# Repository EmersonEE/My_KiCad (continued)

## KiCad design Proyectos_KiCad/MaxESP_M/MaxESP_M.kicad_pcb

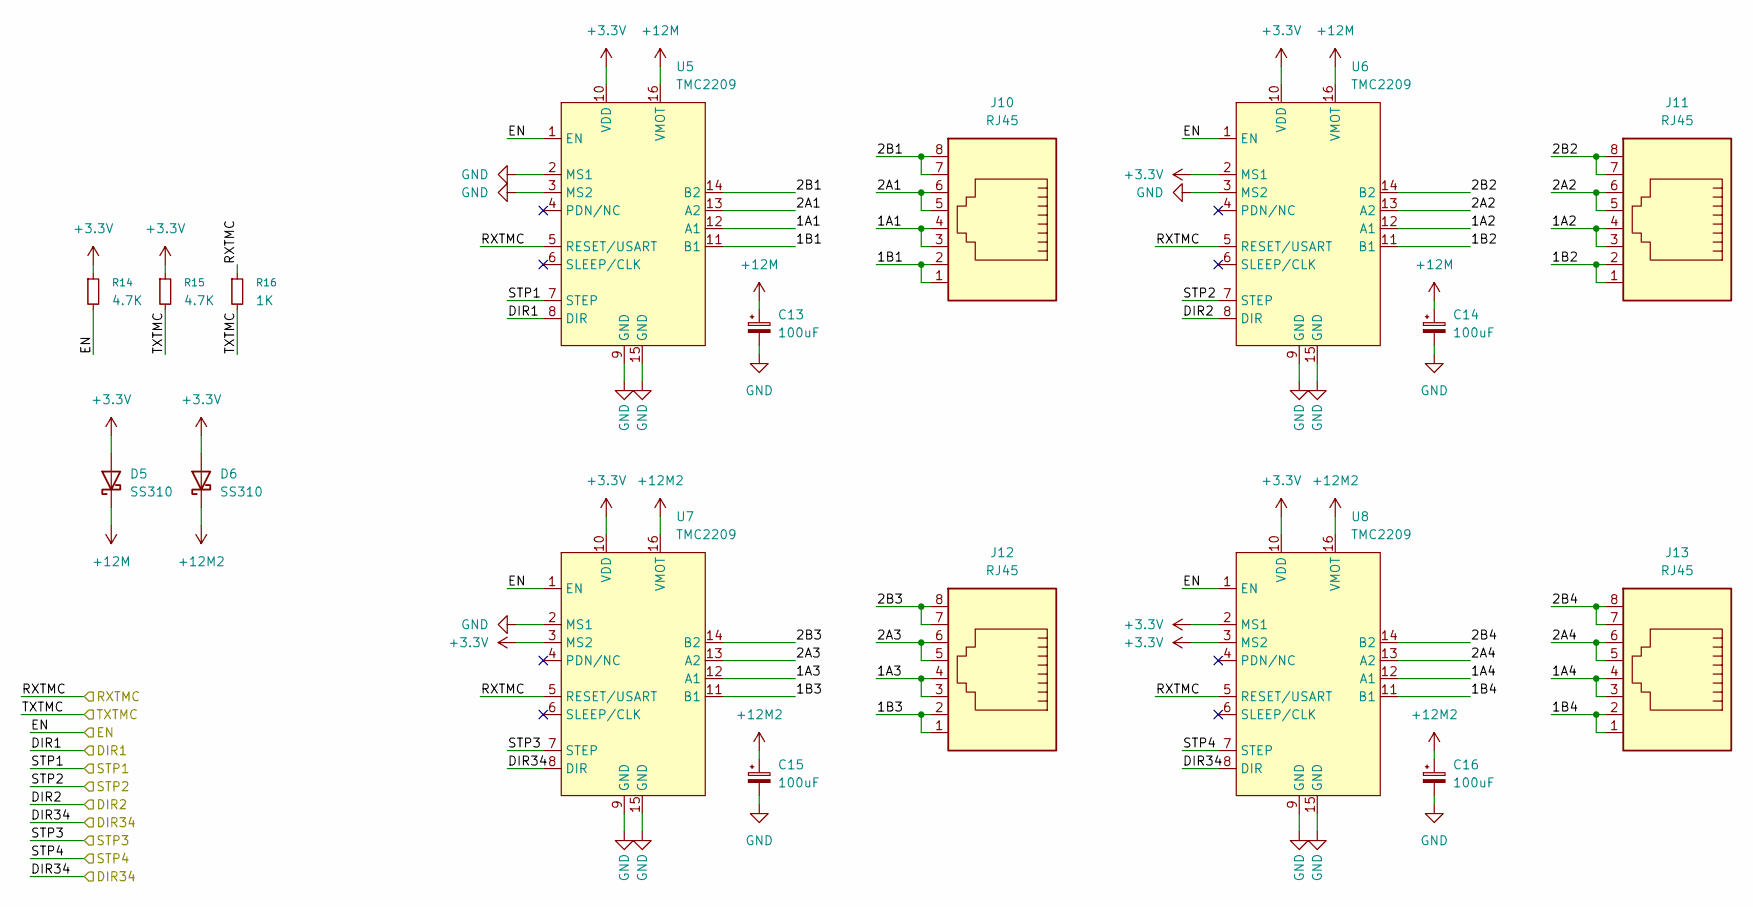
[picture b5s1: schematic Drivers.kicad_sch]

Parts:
C13, C14, C15, C16: 100uF; C_Elec_8x10.2
D5, D6: SS310; D_SMA
J10, J11, J12, J13: RJ45; RJ45_Amphenol_54602-x08_Horizontal
R14, R15: 4.7K; R_0805_2012Metric_Pad1.20x1.40mm_HandSolder
R16: 1K; R_0805_2012Metric_Pad1.20x1.40mm_HandSolder
U5, U6, U7, U8: TMC2209; D_TMC2209_Or

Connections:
+3.3V: D5.2 (A), D6.2 (A), R14.1, R15.1, U5.10 (VDD), U6.2 (MS1), U6.10 (VDD), U7.3 (MS2), U7.10 (VDD), U8.2 (MS1), U8.3 (MS2), U8.10 (VDD); also elsewhere on the board
+12M: C13.1, C14.1, D5.1 (K), U5.16 (VMOT), U6.16 (VMOT); also elsewhere on the board
+12M2: C15.1, C16.1, D6.1 (K), U7.16 (VMOT), U8.16 (VMOT); also elsewhere on the board
/Drivers/1A1: J10.3, J10.4, U5.12 (A1)
/Drivers/1A2: J11.3, J11.4, U6.12 (A1)
/Drivers/1A3: J12.3, J12.4, U7.12 (A1)
/Drivers/1A4: J13.3, J13.4, U8.12 (A1)
/Drivers/1B1: J10.1, J10.2, U5.11 (B1)
/Drivers/1B2: J11.1, J11.2, U6.11 (B1)
/Drivers/1B3: J12.1, J12.2, U7.11 (B1)
/Drivers/1B4: J13.1, J13.2, U8.11 (B1)
/Drivers/2A1: J10.5, J10.6, U5.13 (A2)
/Drivers/2A2: J11.5, J11.6, U6.13 (A2)
/Drivers/2A3: J12.5, J12.6, U7.13 (A2)
/Drivers/2A4: J13.5, J13.6, U8.13 (A2)
/Drivers/2B1: J10.7, J10.8, U5.14 (B2)
/Drivers/2B2: J11.7, J11.8, U6.14 (B2)
/Drivers/2B3: J12.7, J12.8, U7.14 (B2)
/Drivers/2B4: J13.7, J13.8, U8.14 (B2)
/Drivers/DIR1: U5.8 (DIR); also elsewhere on the board
/Drivers/DIR2: U6.8 (DIR); also elsewhere on the board
/Drivers/DIR34: U7.8 (DIR), U8.8 (DIR); also elsewhere on the board
/Drivers/EN: R14.2, U5.1 (EN), U6.1 (EN), U7.1 (EN), U8.1 (EN); also elsewhere on the board
/Drivers/RXTMC: R16.1, U5.5 (RESET/USART), U6.5 (RESET/USART), U7.5 (RESET/USART), U8.5 (RESET/USART); also elsewhere on the board
/Drivers/STP1: U5.7 (STEP); also elsewhere on the board
/Drivers/STP2: U6.7 (STEP); also elsewhere on the board
/Drivers/STP3: U7.7 (STEP); also elsewhere on the board
/Drivers/STP4: U8.7 (STEP); also elsewhere on the board
/Drivers/TXTMC: R15.2, R16.2; also elsewhere on the board
GND: C13.2, C14.2, C15.2, C16.2, U5.2 (MS1), U5.3 (MS2), U5.9 (GND), U5.15 (GND), U6.3 (MS2), U6.9 (GND), U6.15 (GND), U7.2 (MS1), U7.9 (GND), U7.15 (GND), U8.9 (GND), U8.15 (GND); also elsewhere on the board

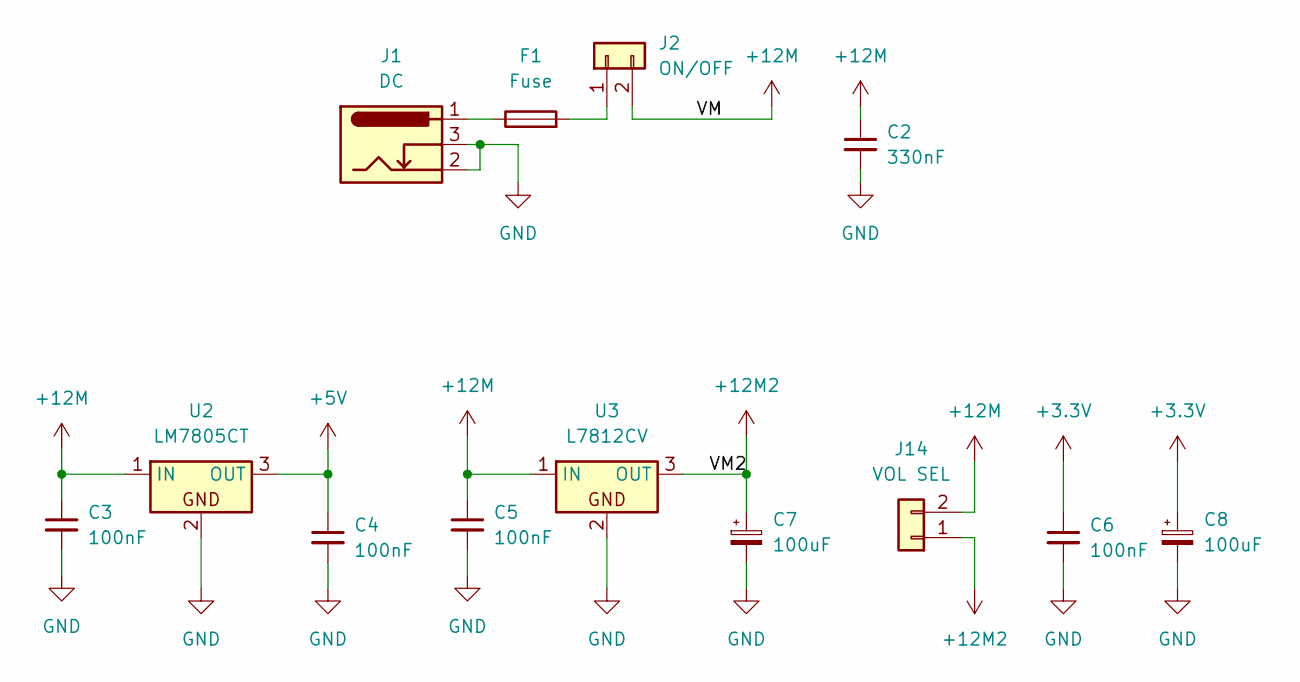
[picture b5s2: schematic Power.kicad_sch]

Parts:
C2: 330nF; C_0805_2012Metric_Pad1.18x1.45mm
C3, C4, C5, C6: 100nF; C_0805_2012Metric_Pad1.18x1.45mm
C7, C8: 100uF; C_0805_2012Metric_Pad1.18x1.45mm
F1: Fuse; Fuse_5x22mm
J1: DC; BarrelJack_Horizontal
J2: ON/OFF; Molex_KK-254_AE-6410-02A_1x02_P2.54mm_Vertical
J14: VOL SEL; PinHeader_1x02_P2.54mm_Vertical
U2: LM7805CT; TO-220-3_Vertical
U3: L7812CV; TO-220-3_Vertical

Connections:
+3.3V: C6.1, C8.1; also elsewhere on the board
+5V: C4.1, U2.3 (OUT); also elsewhere on the board
+12M: C2.1, C3.1, C5.1, J2.2, J14.2, U2.1 (IN), U3.1 (IN); also elsewhere on the board
+12M2: C7.1, J14.1, U3.3 (OUT); also elsewhere on the board
GND: C2.2, C3.2, C4.2, C5.2, C6.2, C7.2, C8.2, J1.2, J1.3, U2.2, U3.2; also elsewhere on the board
unnamed: F1.1, J1.1
unnamed: F1.2, J2.1

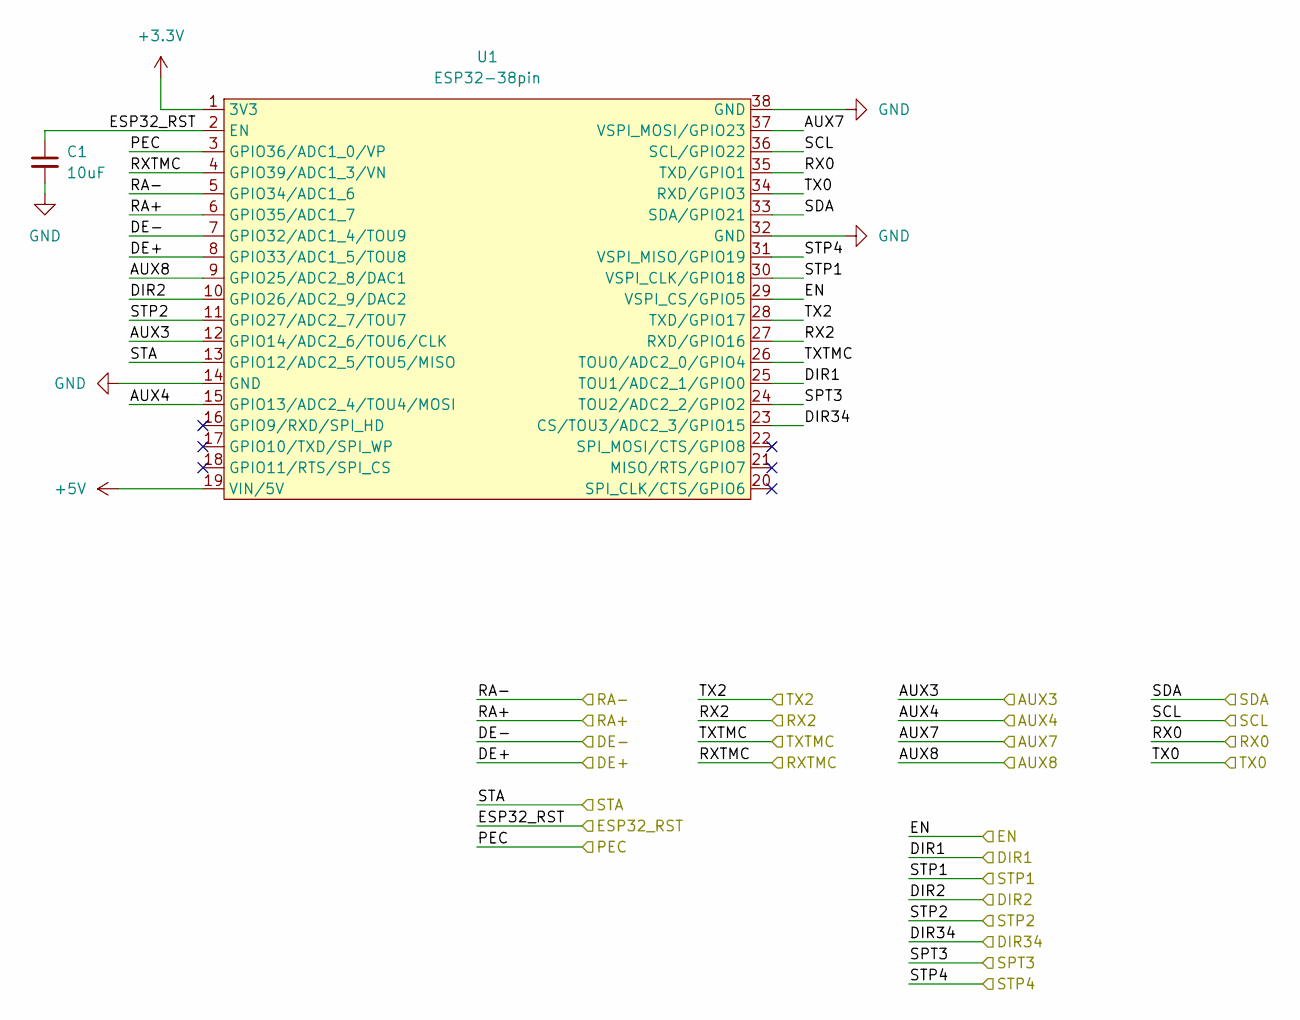
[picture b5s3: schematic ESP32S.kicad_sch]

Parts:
C1: 10uF; C_Elec_8x6.2
U1: ESP32-38pin; NODEMCU-ESP32S-NARROW

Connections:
+3.3V: U1.1 (3V3); also elsewhere on the board
+5V: U1.19 (VIN/5V); also elsewhere on the board
/Drivers/DIR1: U1.25 (TOU1/ADC2_1/GPIO0); also elsewhere on the board
/Drivers/DIR2: U1.10 (GPIO26/ADC2_9/DAC2); also elsewhere on the board
/Drivers/DIR34: U1.23 (CS/TOU3/ADC2_3/GPIO15); also elsewhere on the board
/Drivers/EN: U1.29 (VSPI_CS/GPIO5); also elsewhere on the board
/Drivers/RXTMC: U1.4 (GPIO39/ADC1_3/VN); also elsewhere on the board
/Drivers/STP1: U1.30 (VSPI_CLK/GPIO18); also elsewhere on the board
/Drivers/STP2: U1.11 (GPIO27/ADC2_7/TOU7); also elsewhere on the board
/Drivers/STP3: U1.24 (TOU2/ADC2_2/GPIO2); also elsewhere on the board
/Drivers/STP4: U1.31 (VSPI_MISO/GPIO19); also elsewhere on the board
/Drivers/TXTMC: U1.26 (TOU0/ADC2_0/GPIO4); also elsewhere on the board
/ESP32S/AUX3: U1.12 (GPIO14/ADC2_6/TOU6/CLK); also elsewhere on the board
/ESP32S/AUX4: U1.15 (GPIO13/ADC2_4/TOU4/MOSI); also elsewhere on the board
/ESP32S/AUX7: U1.37 (VSPI_MOSI/GPIO23); also elsewhere on the board
/ESP32S/AUX8: U1.9 (GPIO25/ADC2_8/DAC1); also elsewhere on the board
/ESP32S/DE+: U1.8 (GPIO33/ADC1_5/TOU8); also elsewhere on the board
/ESP32S/DE-: U1.7 (GPIO32/ADC1_4/TOU9); also elsewhere on the board
/ESP32S/ESP32_RST: C1.1, U1.2 (EN)
/ESP32S/PEC: U1.3 (GPIO36/ADC1_0/VP); also elsewhere on the board
/ESP32S/RA+: U1.6 (GPIO35/ADC1_7); also elsewhere on the board
/ESP32S/RA-: U1.5 (GPIO34/ADC1_6); also elsewhere on the board
/ESP32S/RX0: U1.35 (TXD/GPIO1)
/ESP32S/RX2: U1.27 (RXD/GPIO16); also elsewhere on the board
/ESP32S/SCL: U1.36 (SCL/GPIO22); also elsewhere on the board
/ESP32S/SDA: U1.33 (SDA/GPIO21); also elsewhere on the board
/ESP32S/STA: U1.13 (GPIO12/ADC2_5/TOU5/MISO); also elsewhere on the board
/ESP32S/TX0: U1.34 (RXD/GPIO3)
/ESP32S/TX2: U1.28 (TXD/GPIO17); also elsewhere on the board
GND: C1.2, U1.14 (GND), U1.32 (GND), U1.38 (GND); also elsewhere on the board

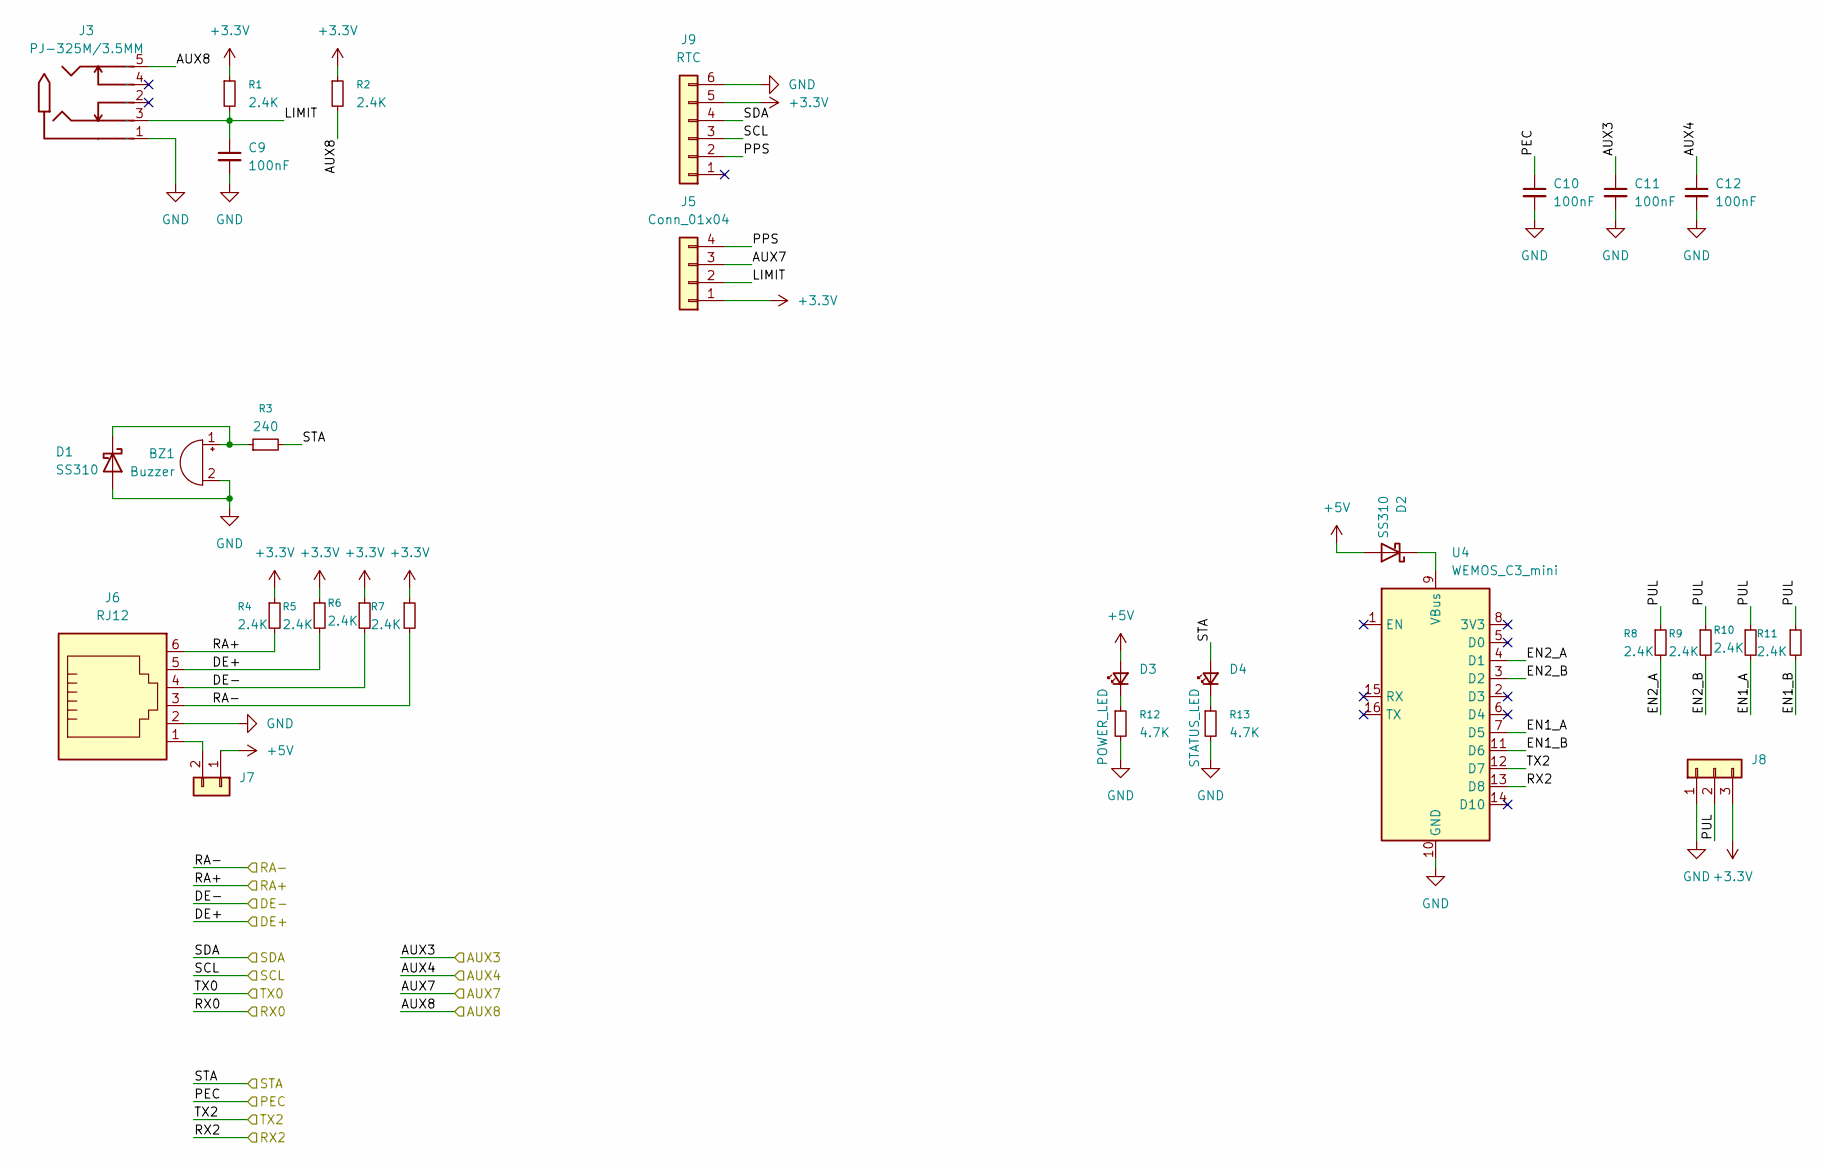
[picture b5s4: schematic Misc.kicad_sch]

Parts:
BZ1: Buzzer; Buzzer_12x9.5RM7.6
C9, C10, C11, C12: 100nF; C_0805_2012Metric_Pad1.18x1.45mm
D1, D2: SS310; D_SMA
D3: POWER_LED; LED_0805_2012Metric_Pad1.15x1.40mm
D4: STATUS_LED; LED_0805_2012Metric_Pad1.15x1.40mm
J3: PJ-325M/3.5MM; Jack_3.5mm_CUI_SJ1-3535NG_Horizontal; Manufacturer Part PJ-325M/3.5MM
J5: Conn_01x04; PinHeader_1x04_P2.54mm_Vertical
J6: RJ12; RJ12_Amphenol_54601-x06_Horizontal
J7: Molex_KK-254_AE-6410-02A_1x02_P2.54mm_Vertical
J8: PinHeader_1x03_P2.54mm_Vertical
J9: RTC; DS3231-RTC-24C32-EEPROM-SINGLE-HEADER
R1, R2, R4, R5, R6, R7, R8, R9, R10, R11: 2.4K; R_0805_2012Metric_Pad1.20x1.40mm_HandSolder
R3: 240; R_0805_2012Metric_Pad1.20x1.40mm_HandSolder
R12, R13: 4.7K; R_0805_2012Metric_Pad1.20x1.40mm_HandSolder
U4: WEMOS_C3_mini

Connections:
+3.3V: J5.1, J8.3, J9.5, R1.1, R2.1, R4.1, R5.1, R6.1, R7.1; also elsewhere on the board
+5V: D2.2 (A), D3.2 (A), J7.1; also elsewhere on the board
/ESP32S/AUX3: C11.1; also elsewhere on the board
/ESP32S/AUX4: C12.1; also elsewhere on the board
/ESP32S/AUX7: J5.3; also elsewhere on the board
/ESP32S/AUX8: J3.5, R2.2; also elsewhere on the board
/ESP32S/DE+: J6.5, R5.2; also elsewhere on the board
/ESP32S/DE-: J6.4, R6.2; also elsewhere on the board
/ESP32S/PEC: C10.1; also elsewhere on the board
/ESP32S/RA+: J6.6, R4.2; also elsewhere on the board
/ESP32S/RA-: J6.3, R7.2; also elsewhere on the board
/ESP32S/RX2: U4.13 (D8); also elsewhere on the board
/ESP32S/SCL: J9.3; also elsewhere on the board
/ESP32S/SDA: J9.4; also elsewhere on the board
/ESP32S/STA: D4.2 (A), R3.2; also elsewhere on the board
/ESP32S/TX2: U4.12 (D7); also elsewhere on the board
/Misc/EN1_A: R10.2, U4.7 (D5)
/Misc/EN1_B: R11.2, U4.11 (D6)
/Misc/EN2_A: R8.2, U4.4 (D1)
/Misc/EN2_B: R9.2, U4.3 (D2)
/Misc/LIMIT: C9.1, J3.3, J5.2, R1.2
/Misc/PPS: J5.4, J9.2
/Misc/PUL: J8.2, R8.1, R9.1, R10.1, R11.1
GND: BZ1.2 (-), C9.2, C10.2, C11.2, C12.2, D1.2 (A), J3.1, J6.2, J8.1, J9.6, R12.2, R13.2, U4.10 (GND); also elsewhere on the board
unnamed: BZ1.1 (+), D1.1 (K), R3.1
unnamed: D2.1 (K), U4.9 (VBus)
unnamed: D3.1 (K), R12.1
unnamed: D4.1 (K), R13.1
unnamed: J6.1, J7.2

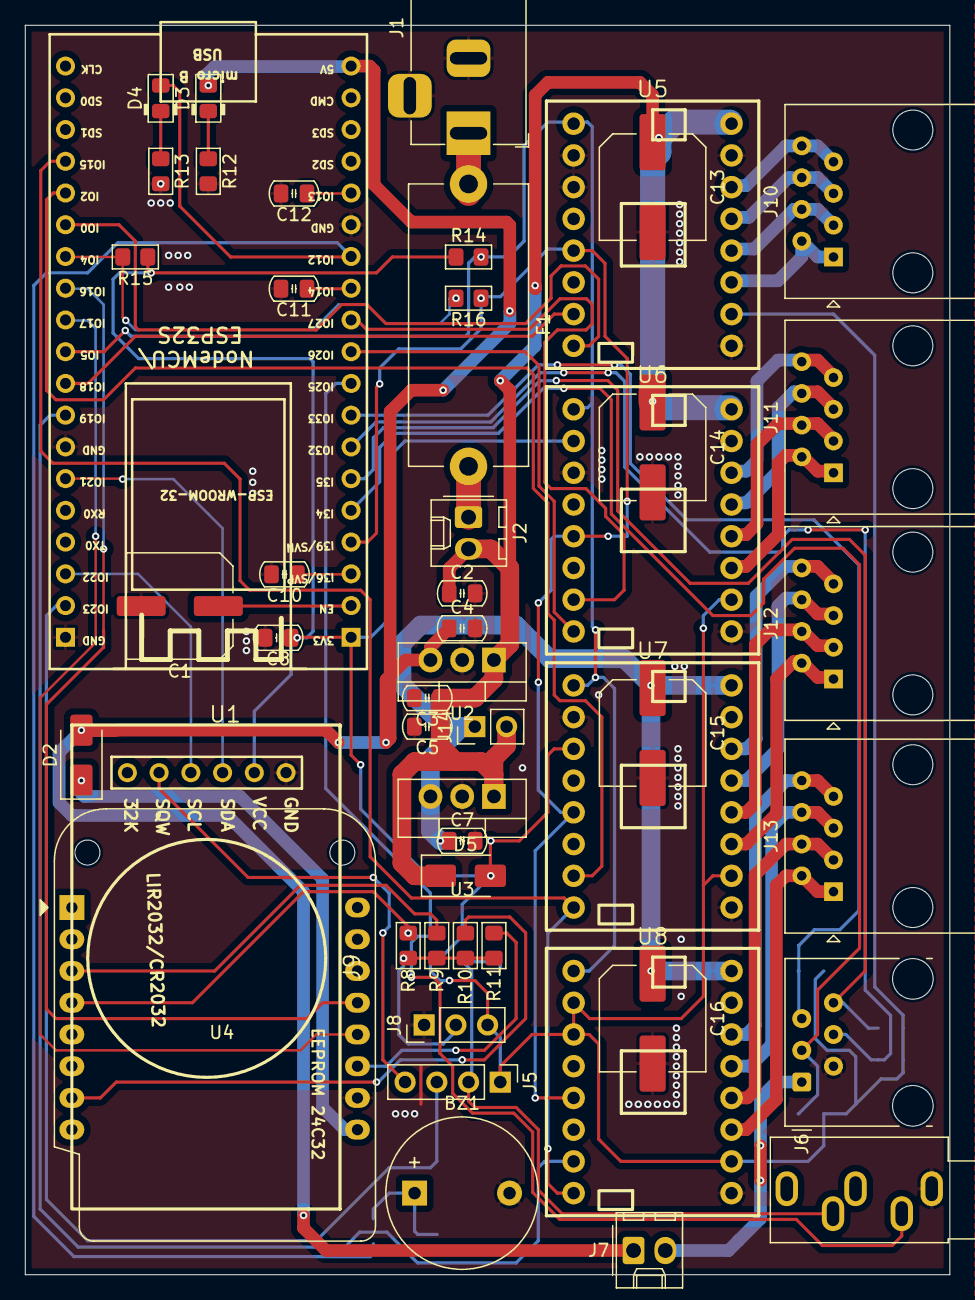
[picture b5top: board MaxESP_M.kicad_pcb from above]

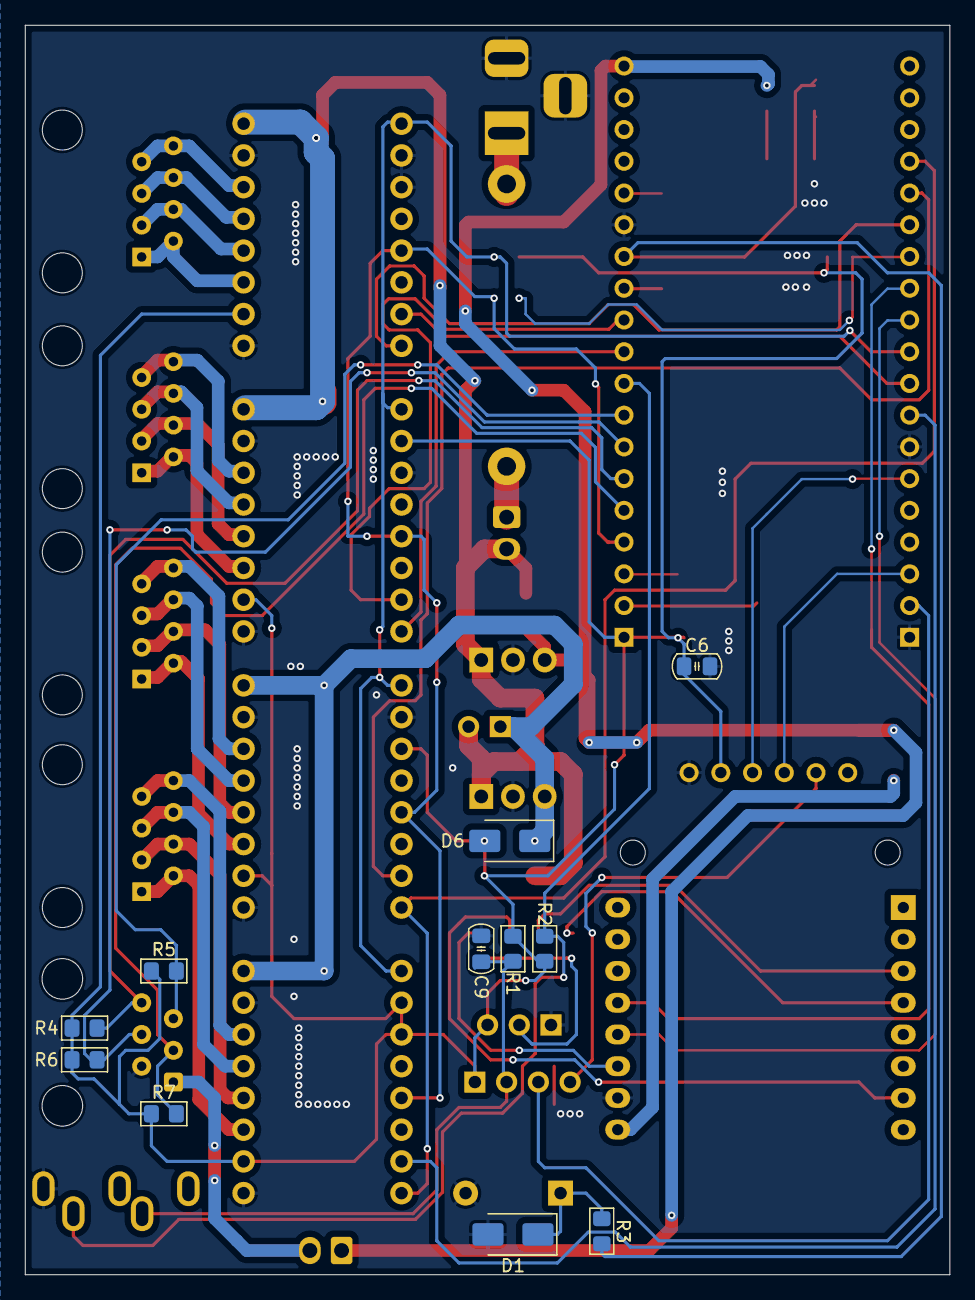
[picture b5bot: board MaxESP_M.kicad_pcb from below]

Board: 2 copper layers, 74.0 x 100.0 mm, 61 parts (11 on the bottom side), 60 nets.

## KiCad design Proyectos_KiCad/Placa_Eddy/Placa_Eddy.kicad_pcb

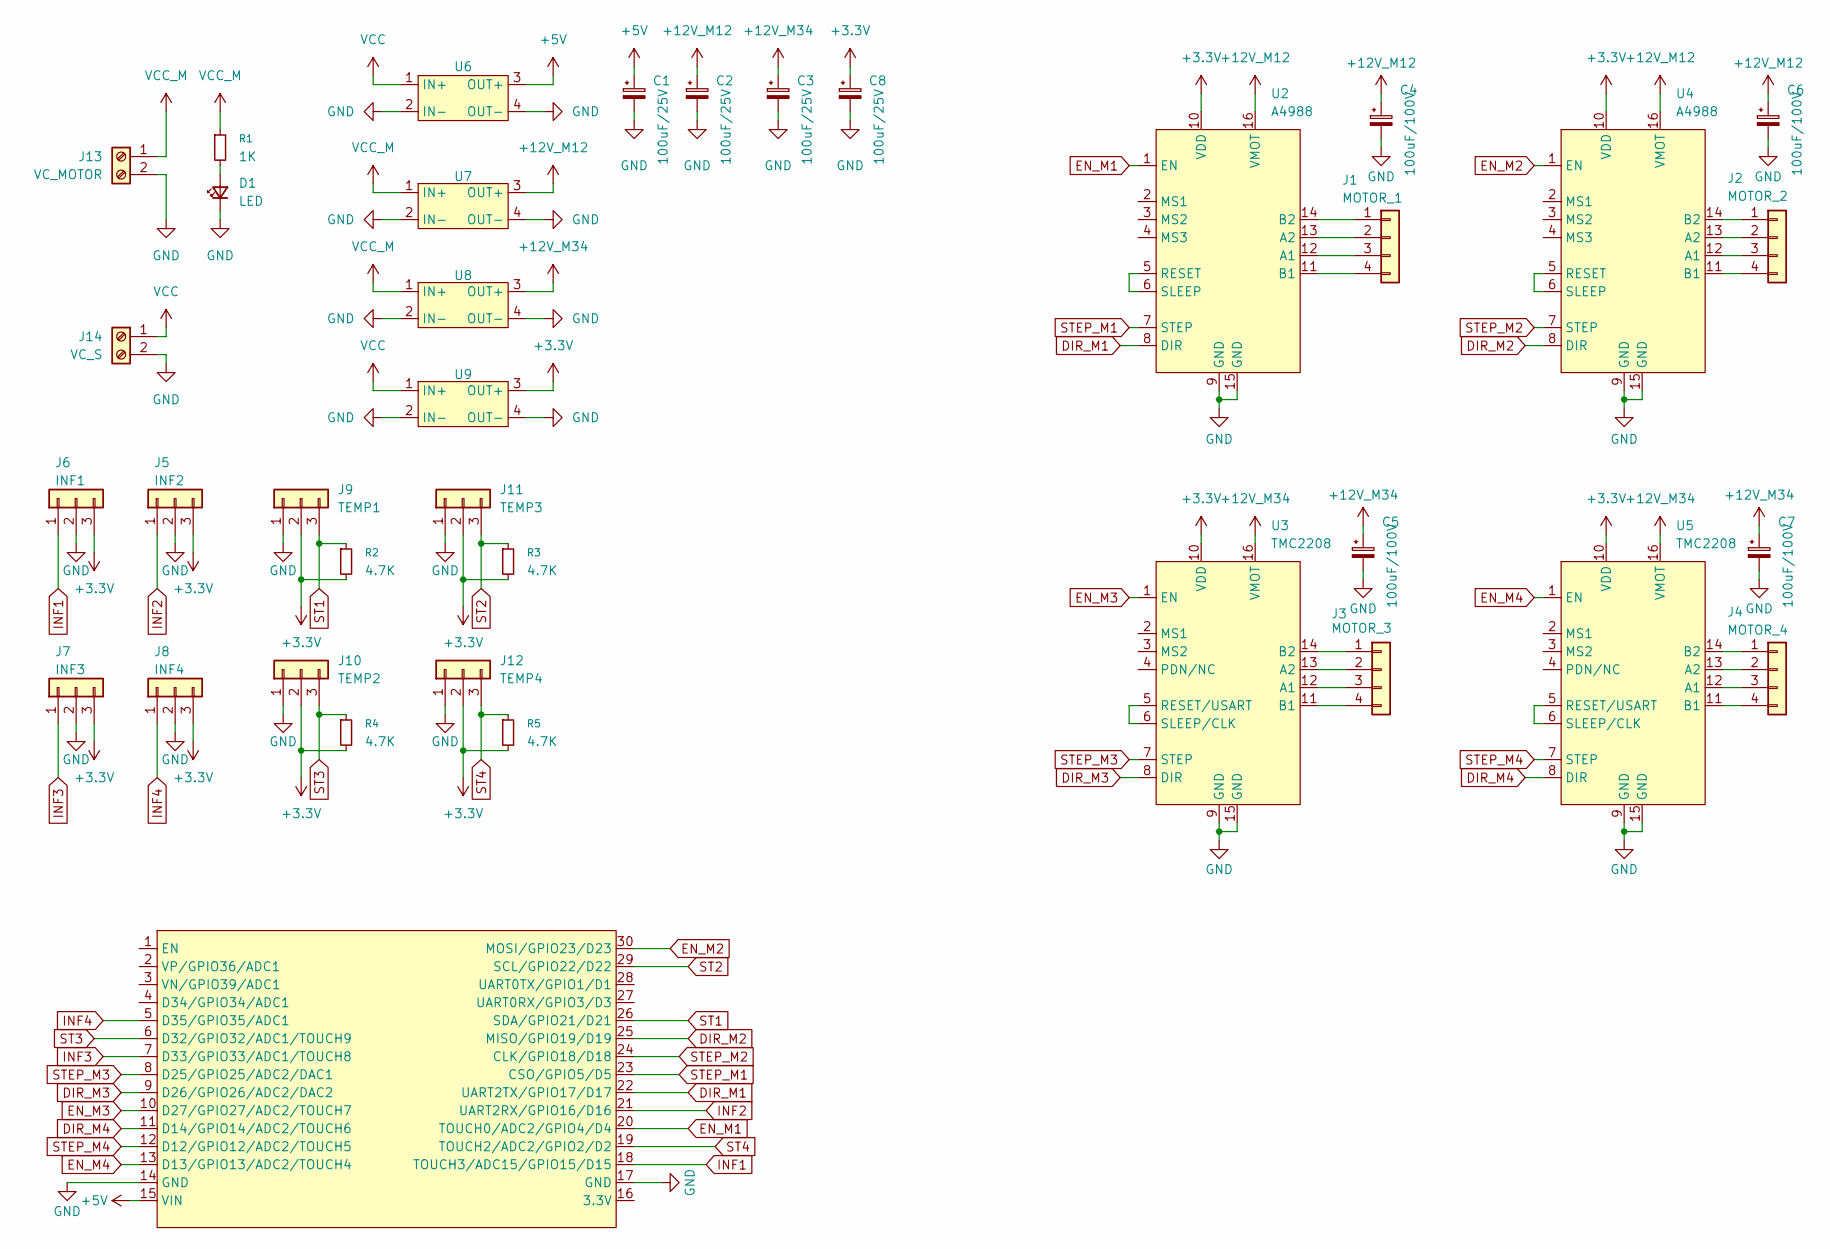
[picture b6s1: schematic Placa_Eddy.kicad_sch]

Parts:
C1, C2, C3, C8: 100uF/25V; CP_Elec_5x5.4
C4, C5, C6, C7: 100uF/100V; CP_Elec_5x5.4
D1: LED; LED_D5.0mm
J1: MOTOR_1; Molex_KK-254_AE-6410-04A_1x04_P2.54mm_Vertical; Part Number 1-0401FBV0T
J2: MOTOR_2; Molex_KK-254_AE-6410-04A_1x04_P2.54mm_Vertical; Part Number 1-0401FBV0T
J3: MOTOR_3; Molex_KK-254_AE-6410-04A_1x04_P2.54mm_Vertical; Part Number 1-0401FBV0T
J4: MOTOR_4; Molex_KK-254_AE-6410-04A_1x04_P2.54mm_Vertical; Part Number 1-0401FBV0T
J5: INF2; Molex_KK-254_AE-6410-03A_1x03_P2.54mm_Vertical; Part Number 1-0301FBV0T
J6: INF1; Molex_KK-254_AE-6410-03A_1x03_P2.54mm_Vertical; Part Number 1-0301FBV0T
J7: INF3; Molex_KK-254_AE-6410-03A_1x03_P2.54mm_Vertical; Part Number 1-0301FBV0T
J8: INF4; Molex_KK-254_AE-6410-03A_1x03_P2.54mm_Vertical; Part Number 1-0301FBV0T
J9: TEMP1; Molex_KK-254_AE-6410-03A_1x03_P2.54mm_Vertical; Part Number 1-0301FBV0T
J10: TEMP2; Molex_KK-254_AE-6410-03A_1x03_P2.54mm_Vertical; Part Number 1-0301FBV0T
J11: TEMP3; Molex_KK-254_AE-6410-03A_1x03_P2.54mm_Vertical; Part Number 1-0301FBV0T
J12: TEMP4; Molex_KK-254_AE-6410-03A_1x03_P2.54mm_Vertical; Part Number 1-0301FBV0T
J13: VC_MOTOR; TerminalBlock_Phoenix_MKDS-1,5-2_1x02_P5.00mm_Horizontal
J14: VC_S; TerminalBlock_Phoenix_MKDS-1,5-2_1x02_P5.00mm_Horizontal
R1: 1K; R_1206_3216Metric_Pad1.30x1.75mm
R2, R3, R4, R5: 4.7K; R_1206_3216Metric_Pad1.30x1.75mm
U1: ESP32_DevKit_V1_DOIT; ESP32_DEVKIT_V1_E32
U2, U4: A4988
U3, U5: TMC2208; D_TMC2209_Ca
U6, U7, U8, U9: LM2596S

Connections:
+3.3V: C8.1, J5.3, J6.3, J7.3, J8.3, J9.2, J10.2, J11.2, J12.2, R2.2, R3.2, R4.2, R5.2, U2.10 (VDD), U3.10 (VDD), U4.10 (VDD), U5.10 (VDD), U9.3 (OUT+)
+5V: C1.1, U1.15 (VIN), U6.3 (OUT+)
+12V_M12: C2.1, C4.1, C6.1, U2.16 (VMOT), U4.16 (VMOT), U7.3 (OUT+)
+12V_M34: C3.1, C5.1, C7.1, U3.16 (VMOT), U5.16 (VMOT), U8.3 (OUT+)
DIR_M1: U1.22 (UART2TX/GPIO17/D17), U2.8 (DIR)
DIR_M2: U1.25 (MISO/GPIO19/D19), U4.8 (DIR)
DIR_M3: U1.9 (D26/GPIO26/ADC2/DAC2), U3.8 (DIR)
DIR_M4: U1.11 (D14/GPIO14/ADC2/TOUCH6), U5.8 (DIR)
EN_M1: U1.20 (TOUCH0/ADC2/GPIO4/D4), U2.1 (EN)
EN_M2: U1.30 (MOSI/GPIO23/D23), U4.1 (EN)
EN_M3: U1.10 (D27/GPIO27/ADC2/TOUCH7), U3.1 (EN)
EN_M4: U1.13 (D13/GPIO13/ADC2/TOUCH4), U5.1 (EN)
GND: C1.2, C2.2, C3.2, C4.2, C5.2, C6.2, C7.2, C8.2, D1.1 (K), J5.2, J6.2, J7.2, J8.2, J9.1, J10.1, J11.1, J12.1, J13.2, J14.2, U1.14 (GND), U1.17 (GND), U2.9 (GND), U2.15 (GND), U3.9 (GND), U3.15 (GND), U4.9 (GND), U4.15 (GND), U5.9 (GND), U5.15 (GND), U6.2 (IN-), U6.4 (OUT-), U7.2 (IN-), U7.4 (OUT-), U8.2 (IN-), U8.4 (OUT-), U9.2 (IN-), U9.4 (OUT-)
INF1: J6.1, U1.18 (TOUCH3/ADC15/GPIO15/D15)
INF2: J5.1, U1.21 (UART2RX/GPIO16/D16)
INF3: J7.1, U1.7 (D33/GPIO33/ADC1/TOUCH8)
INF4: J8.1, U1.5 (D35/GPIO35/ADC1)
unnamed: D1.2 (A), R1.2
unnamed: J1.1, U2.14 (B2)
unnamed: J1.2, U2.13 (A2)
unnamed: J1.3, U2.12 (A1)
unnamed: J1.4, U2.11 (B1)
unnamed: J2.1, U4.14 (B2)
unnamed: J2.2, U4.13 (A2)
unnamed: J2.3, U4.12 (A1)
unnamed: J2.4, U4.11 (B1)
unnamed: J3.1, U3.14 (B2)
unnamed: J3.2, U3.13 (A2)
unnamed: J3.3, U3.12 (A1)
unnamed: J3.4, U3.11 (B1)
unnamed: J4.1, U5.14 (B2)
unnamed: J4.2, U5.13 (A2)
unnamed: J4.3, U5.12 (A1)
unnamed: J4.4, U5.11 (B1)
unnamed: U2.5 (RESET), U2.6 (SLEEP)
unnamed: U3.5 (RESET/USART), U3.6 (SLEEP/CLK)
unnamed: U4.5 (RESET), U4.6 (SLEEP)
unnamed: U5.5 (RESET/USART), U5.6 (SLEEP/CLK)
ST1: J9.3, R2.1, U1.26 (SDA/GPIO21/D21)
ST2: J11.3, R3.1, U1.29 (SCL/GPIO22/D22)
ST3: J10.3, R4.1, U1.6 (D32/GPIO32/ADC1/TOUCH9)
ST4: J12.3, R5.1, U1.19 (TOUCH2/ADC2/GPIO2/D2)
STEP_M1: U1.23 (CSO/GPIO5/D5), U2.7 (STEP)
STEP_M2: U1.24 (CLK/GPIO18/D18), U4.7 (STEP)
STEP_M3: U1.8 (D25/GPIO25/ADC2/DAC1), U3.7 (STEP)
STEP_M4: U1.12 (D12/GPIO12/ADC2/TOUCH5), U5.7 (STEP)
VCC: J14.1, U6.1 (IN+), U9.1 (IN+)
VCC_M: J13.1, R1.1, U7.1 (IN+), U8.1 (IN+)

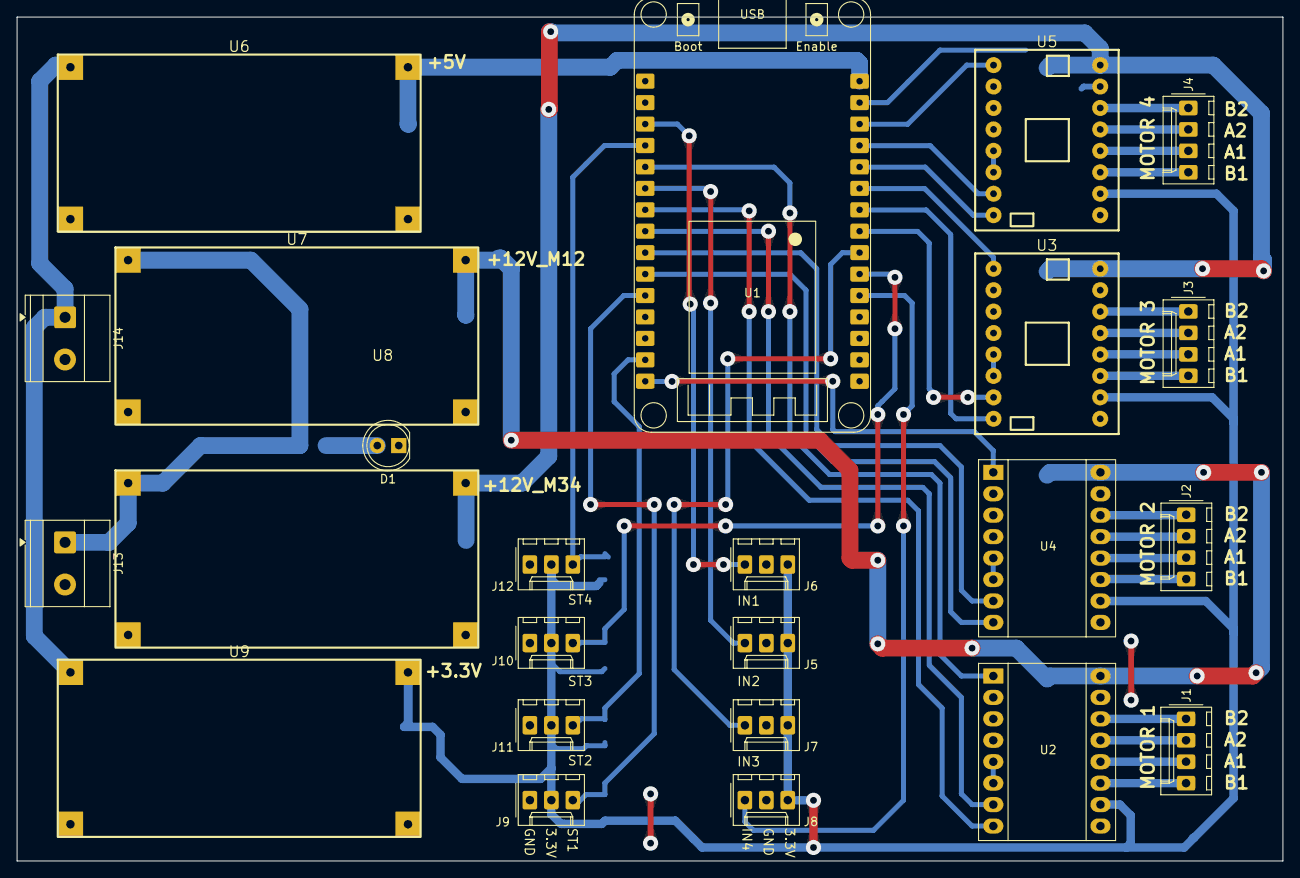
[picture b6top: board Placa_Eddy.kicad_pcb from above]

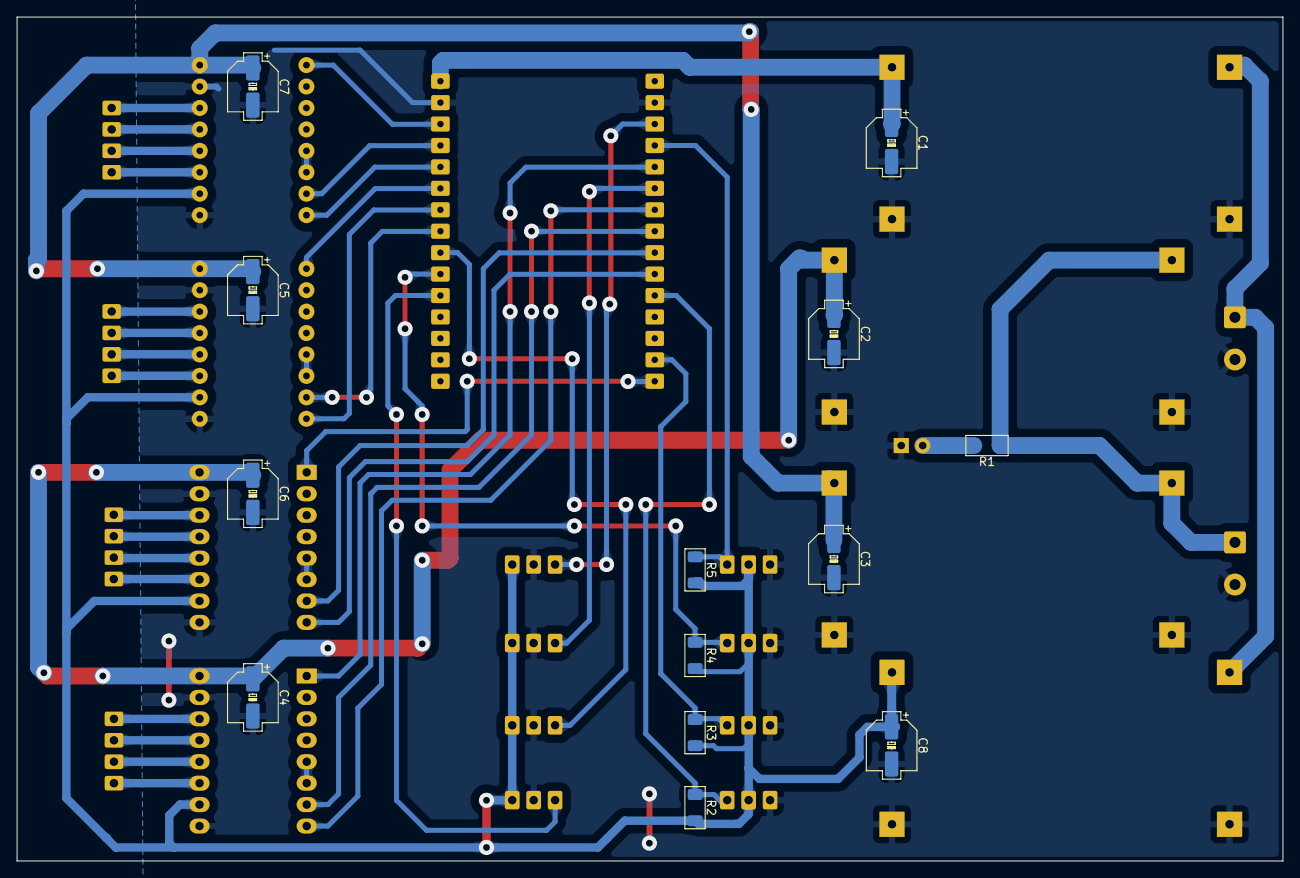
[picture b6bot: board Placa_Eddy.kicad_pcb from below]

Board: 2 copper layers, 150.0 x 100.0 mm, 37 parts (13 on the bottom side), 48 nets.

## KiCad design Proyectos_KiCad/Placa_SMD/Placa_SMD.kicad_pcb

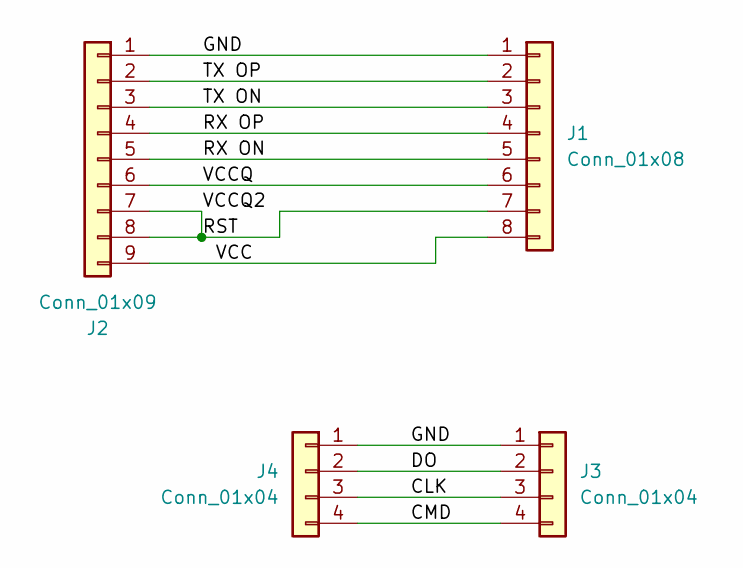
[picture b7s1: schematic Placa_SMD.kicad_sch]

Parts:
J1: Conn_01x08; Conn_01x08_SMD
J2: Conn_01x09; Conn_01x09_SMD
J3, J4: Conn_01x04; Conn_01x04_SMD

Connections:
/CLK: J3.3, J4.3
/CMD: J3.4, J4.4
/DO: J3.2, J4.2
/GND: J1.1, J2.1, J3.1, J4.1
/RST: J1.7, J2.7, J2.8
/RX ON: J1.5, J2.5
/RX OP: J1.4, J2.4
/TX ON: J1.3, J2.3
/TX OP: J1.2, J2.2
/VCC: J1.8, J2.9
/VCCQ: J1.6, J2.6

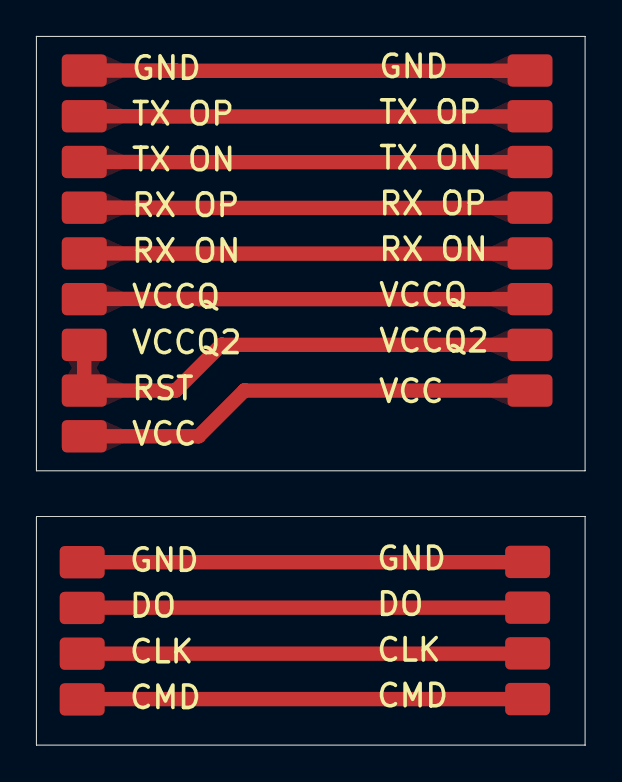
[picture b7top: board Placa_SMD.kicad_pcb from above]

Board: 2 copper layers, 30.5 x 39.4 mm, 4 parts (0 on the bottom side), 11 nets.
